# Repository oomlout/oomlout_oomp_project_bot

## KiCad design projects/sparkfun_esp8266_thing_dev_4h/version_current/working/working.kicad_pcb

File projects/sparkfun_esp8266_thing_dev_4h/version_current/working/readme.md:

# ESP8266_Thing_Dev_4H by sparkfun  
This is a harvested standardized copy of a project from github.  
The original project can be found at:  
https://github.com/sparkfun/ESP8266_Thing_Dev_4H  
Please consult that link for additional, details, files, and license information.  
Note: It was auto harvested and if the original repo had more than one board file or anything out of the ordinary the files here are likely not representative.

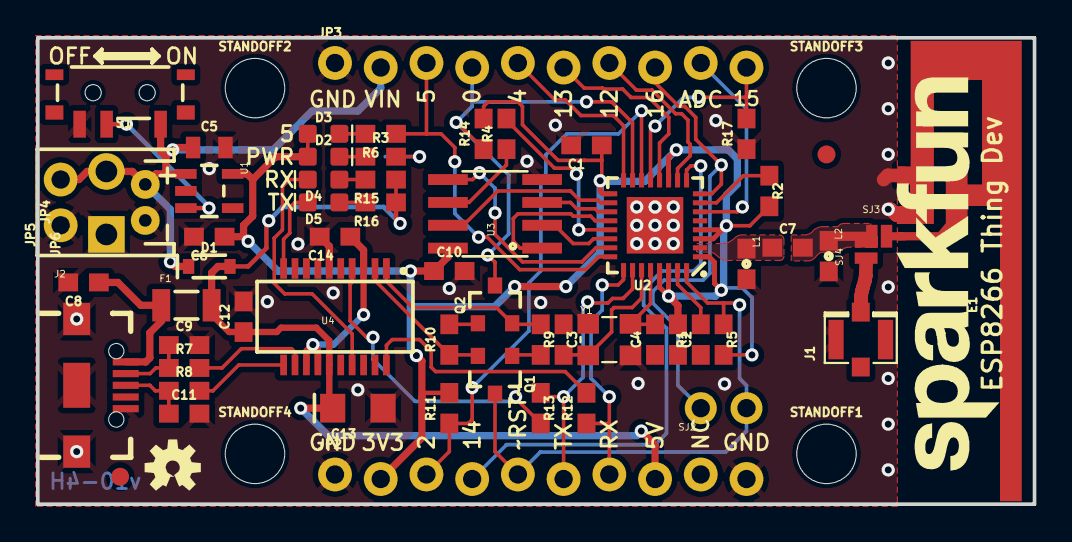
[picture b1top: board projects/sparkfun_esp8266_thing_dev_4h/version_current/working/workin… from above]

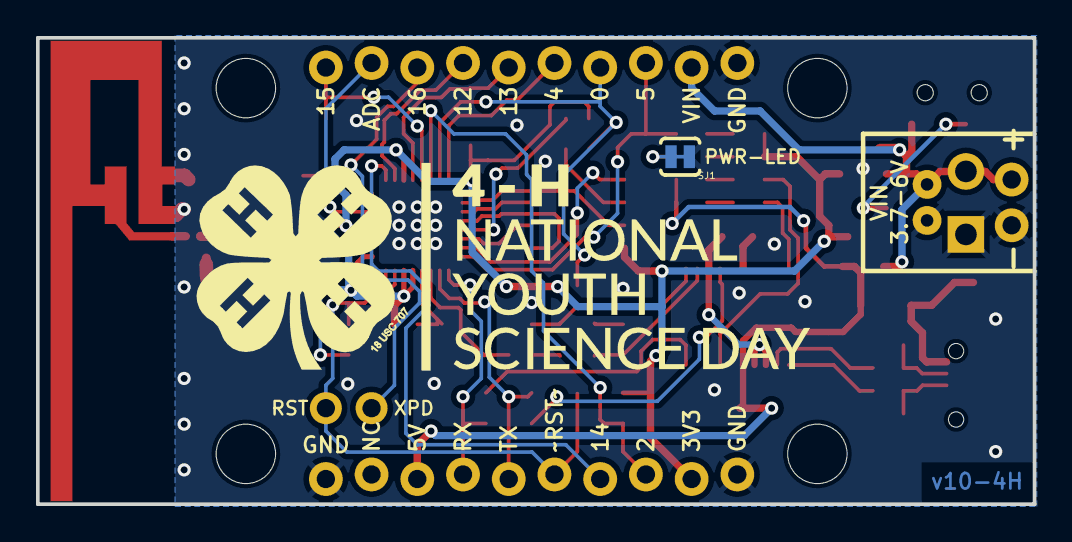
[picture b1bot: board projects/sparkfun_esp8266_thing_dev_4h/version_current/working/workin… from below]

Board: 2 copper layers, 55.4 x 25.9 mm, 70 parts (2 on the bottom side), 52 nets.

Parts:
C1: 10uF; 0603
C2, C8, C10, C12, C14: 0.1uF; 0603
C3, C4: 10pF; 0603
C5: 1.0uF; 0805
C6: 2.2uF; 0603
C7: 5.6PF; 0603
C9, C11: 47pF; 0603
C13: 10uF; EIA3216
D1: 1A/23V/620mV; SOD-323
D2: RED; LED-0603
D3: BLUE; LED-0603
D4: Yellow; LED-0603
D5: GREEN; LED-0603
E1: TRACE_ANTENNA_2.4GHZ_25.7MM
F1: 500mA; PTC-1206
FID1, FID2: FIDUCIAL1X2; FIDUCIAL-1X2
FRAME1: FRAME-LETTER; CREATIVE_COMMONS
J1: U.FL
J2: USB-B-MICRO-SMD_V03
JP2, JP3: 1X10_LOCK_NS
JP4: JST-2-PTH
JP5: 1X02_NO_SILK
JP6: SCREWTERMINAL-3.5MM-2-NS
L1, L2: DNP; 0603
LOGO1: SFE_LOGO_NAME.2_INCH; SFE_LOGO_NAME_.2
LOGO2: OSHW-LOGOS; OSHW-LOGO-S
Q1, Q2: 600mA/40V; SOT23-3
R1: 12k; 0603
R2, R5, R9, R10, R11, R14, R17: 10k; 0603
R3, R4, R6: 200; 0603
R7, R8: 27; 0603
R12, R13, R15, R16: 1k; 0603
S1: SWITCH_SPST_SMD_A
SJ1: PWRLED; PAD-JUMPER-2-NC_BY_TRACE_YES_SILK
SJ2: SLEEP-PTH; PTH-JUMPER-2-NO_NO_SILK
SJ3: TRACE; PAD-JUMPER-2-NC_BY_PASTE_NO_SILK
SJ4: U.FL; PAD-JUMPER-2-NO_NO_SILK
STANDOFF1, STANDOFF2, STANDOFF3, STANDOFF4: STAND-OFF
U1: AP2112K-3.3V; SOT23-5
U2: ESP8266; QFN32-5X5MM
U3: AT25SF041-SOIC8; SO08
U4: FTS31XS-U; SSOP20_L
U$1: 4H-NYSD-LOGO-1.35IN; 4H-1.35IN_WIDE
U$2: SPECIAL_INSTRUCTIONS-ORDERING; ORDERING_INSTRUCTIONS
Y1: 26MHz; CRYSTAL-SMD-3.2X2.5

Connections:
3.3V_F: C14.1, U4.3, U4.13, U4.14
ADC: JP3.9, U2.6
ANT: J1.P$3, SJ4.1
CHIP_EN: R2.1, U2.7
D+: C11.1, J2.D+, R8.1
D-: C9.1, J2.D-, R7.1
DTR: Q2.2, R9.1, U4.1
GND: C1.2, C2.2, C3.1, C4.1, C5.2, C6.2, C8.2, C9.2, C10.2, C11.2, C12.2, C13.-, C14.2, E1.GND, E1.GND2, J1.P$1, J1.P$2, J2.GND, J2.SHIELD1, J2.SHIELD2, J2.SHIELD3, JP2.1, JP2.10, JP3.1, JP4.1, JP5.1, JP6.1, L1.2, L2.2, R1.1, R17.1, S1.1, SJ1.1, U1.2, U2.EP, U3.4, U4.6, U4.16, Y1.2, Y1.4
GPIO0: JP3.4, Q2.3, R14.1, U2.15
GPIO2: JP2.3, R11.1, U2.14
GPIO4: JP3.5, U2.16
GPIO5: JP3.3, R6.1, U2.24
GPIO12: JP3.7, U2.10
GPIO13: JP3.6, U2.12
GPIO14: JP2.4, U2.9
GPIO15: JP3.10, R17.2, U2.13
GPIO16: JP3.8, SJ2.1, U2.8
LNA: C7.1, L1.1, U2.2
LNA2: C7.2, L2.1, SJ3.1, SJ4.2
unnamed: R1.2, U2.31
unnamed: C4.2, U2.28, Y1.3
unnamed: C3.2, U2.27, Y1.1
unnamed: R7.2, U4.12
unnamed: R3.2, SJ1.2
unnamed: Q1.1, R9.2
unnamed: R8.2, U4.11
unnamed: D5.A, R16.2
unnamed: D3.C, R6.2
unnamed: D4.A, R15.2
unnamed: D2.C, R3.1
unnamed: Q2.1, R10.2
unnamed: S1.2, U1.3
RESET: JP2.5, Q1.3, R5.1, SJ2.2, U2.32
RTS: Q1.2, R10.1, U4.2
RXD: R13.2, U4.4
RXLED: D4.C, U4.17
SD_CLK: R4.1, U3.6
SD_CLK0: R4.2, U2.21
SD_CS0: U2.20, U3.1
SD_SI: U2.23, U3.5
SD_SO: U2.22, U3.2
SD_~HD: U2.18, U3.7
SD_~WP: U2.19, U3.3
TRACE_ANT: E1.ANT, SJ3.2
TXD: R12.2, U4.20
TXLED: D5.C, U4.10
U0RXI: JP2.7, R12.1, U2.25
U0TXO: JP2.6, R13.1, U2.26
USBVCC: C12.1, C13.+, D1.A, F1.2, JP2.8, R15.1, R16.1, U4.15
VCC: C1.1, C2.1, C6.1, C10.1, D2.A, D3.A, JP2.2, R2.2, R5.2, R11.2, R14.2, U1.5, U2.1, U2.3, U2.4, U2.11, U2.17, U2.29, U2.30, U3.8
VIN: C5.1, D1.C, JP3.2, JP4.2, JP5.2, JP6.2, S1.3, U1.1
VUSB: C8.1, F1.1, J2.VBUS

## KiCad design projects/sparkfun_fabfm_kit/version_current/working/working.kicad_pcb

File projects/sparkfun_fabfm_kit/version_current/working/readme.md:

# OOMP Project  
## fabFM-Kit  by sparkfun  
  
oomp key: oomp_projects_flat_sparkfun_fabfm_kit  
(snippet of original readme)  
  
**NOTE:** *This product has been retired from our catalog. If you are looking for more up-to-date info, please check out some of these resources to see how other users are still hacking and improving on this product.*  
* *[SparkFun Forum](https://forum.sparkfun.com/)*  
* *[IRC Channel](https://www.sparkfun.com/news/263)*  
  
FabFM Radio Kit  
===============  
  
[    
*FabFM Radio Kit (KIT-11043)*](https://www.sparkfun.com/products/11043)  
  
The FabFM is a stylish FM radio kit that can be built with just basic soldering tools. The PCB is all PTH, meaning that even a beginner solderer can put this kit together with a little time. The wooden, laser cut frame doesn't take any tools or glue to put together, each part press-fits into another. Once assembled the FabFM Radio Kit produces a fully functioning, old-school style FM radio.  
  
[*See the wiki for assembly instuctions.*](https://github.com/sparkfun/fabFM-Kit/wiki)  
  
Repository Contents  
-------------------  
  
* **/enclosure** - Vector files for the enclosure  
* **/firmware** - Arduino sketch that is loaded onto the ATMega328  
* **/hardware** - Eagle PCB layout files  
  
License Information  
-------------------  
  
All contents of this repository are released under [Creative Commons Share-alike 3.0](http://creativecommons.org/licenses/by-sa/3.0/).  
  
Authors: Aaron Weiss @ SparkFun Electonics, Original Design by David Mellis and Dana Gordon  
  
  full source readme at [readme_src.md](readme_src.md)  
  
source repo at: [https://github.com/sparkfun/fabFM-Kit](https://github.com/sparkfun/fabFM-Kit)  
## Board  

## Schematic  

[schematic pdf](working_schematic.pdf)  
## Images

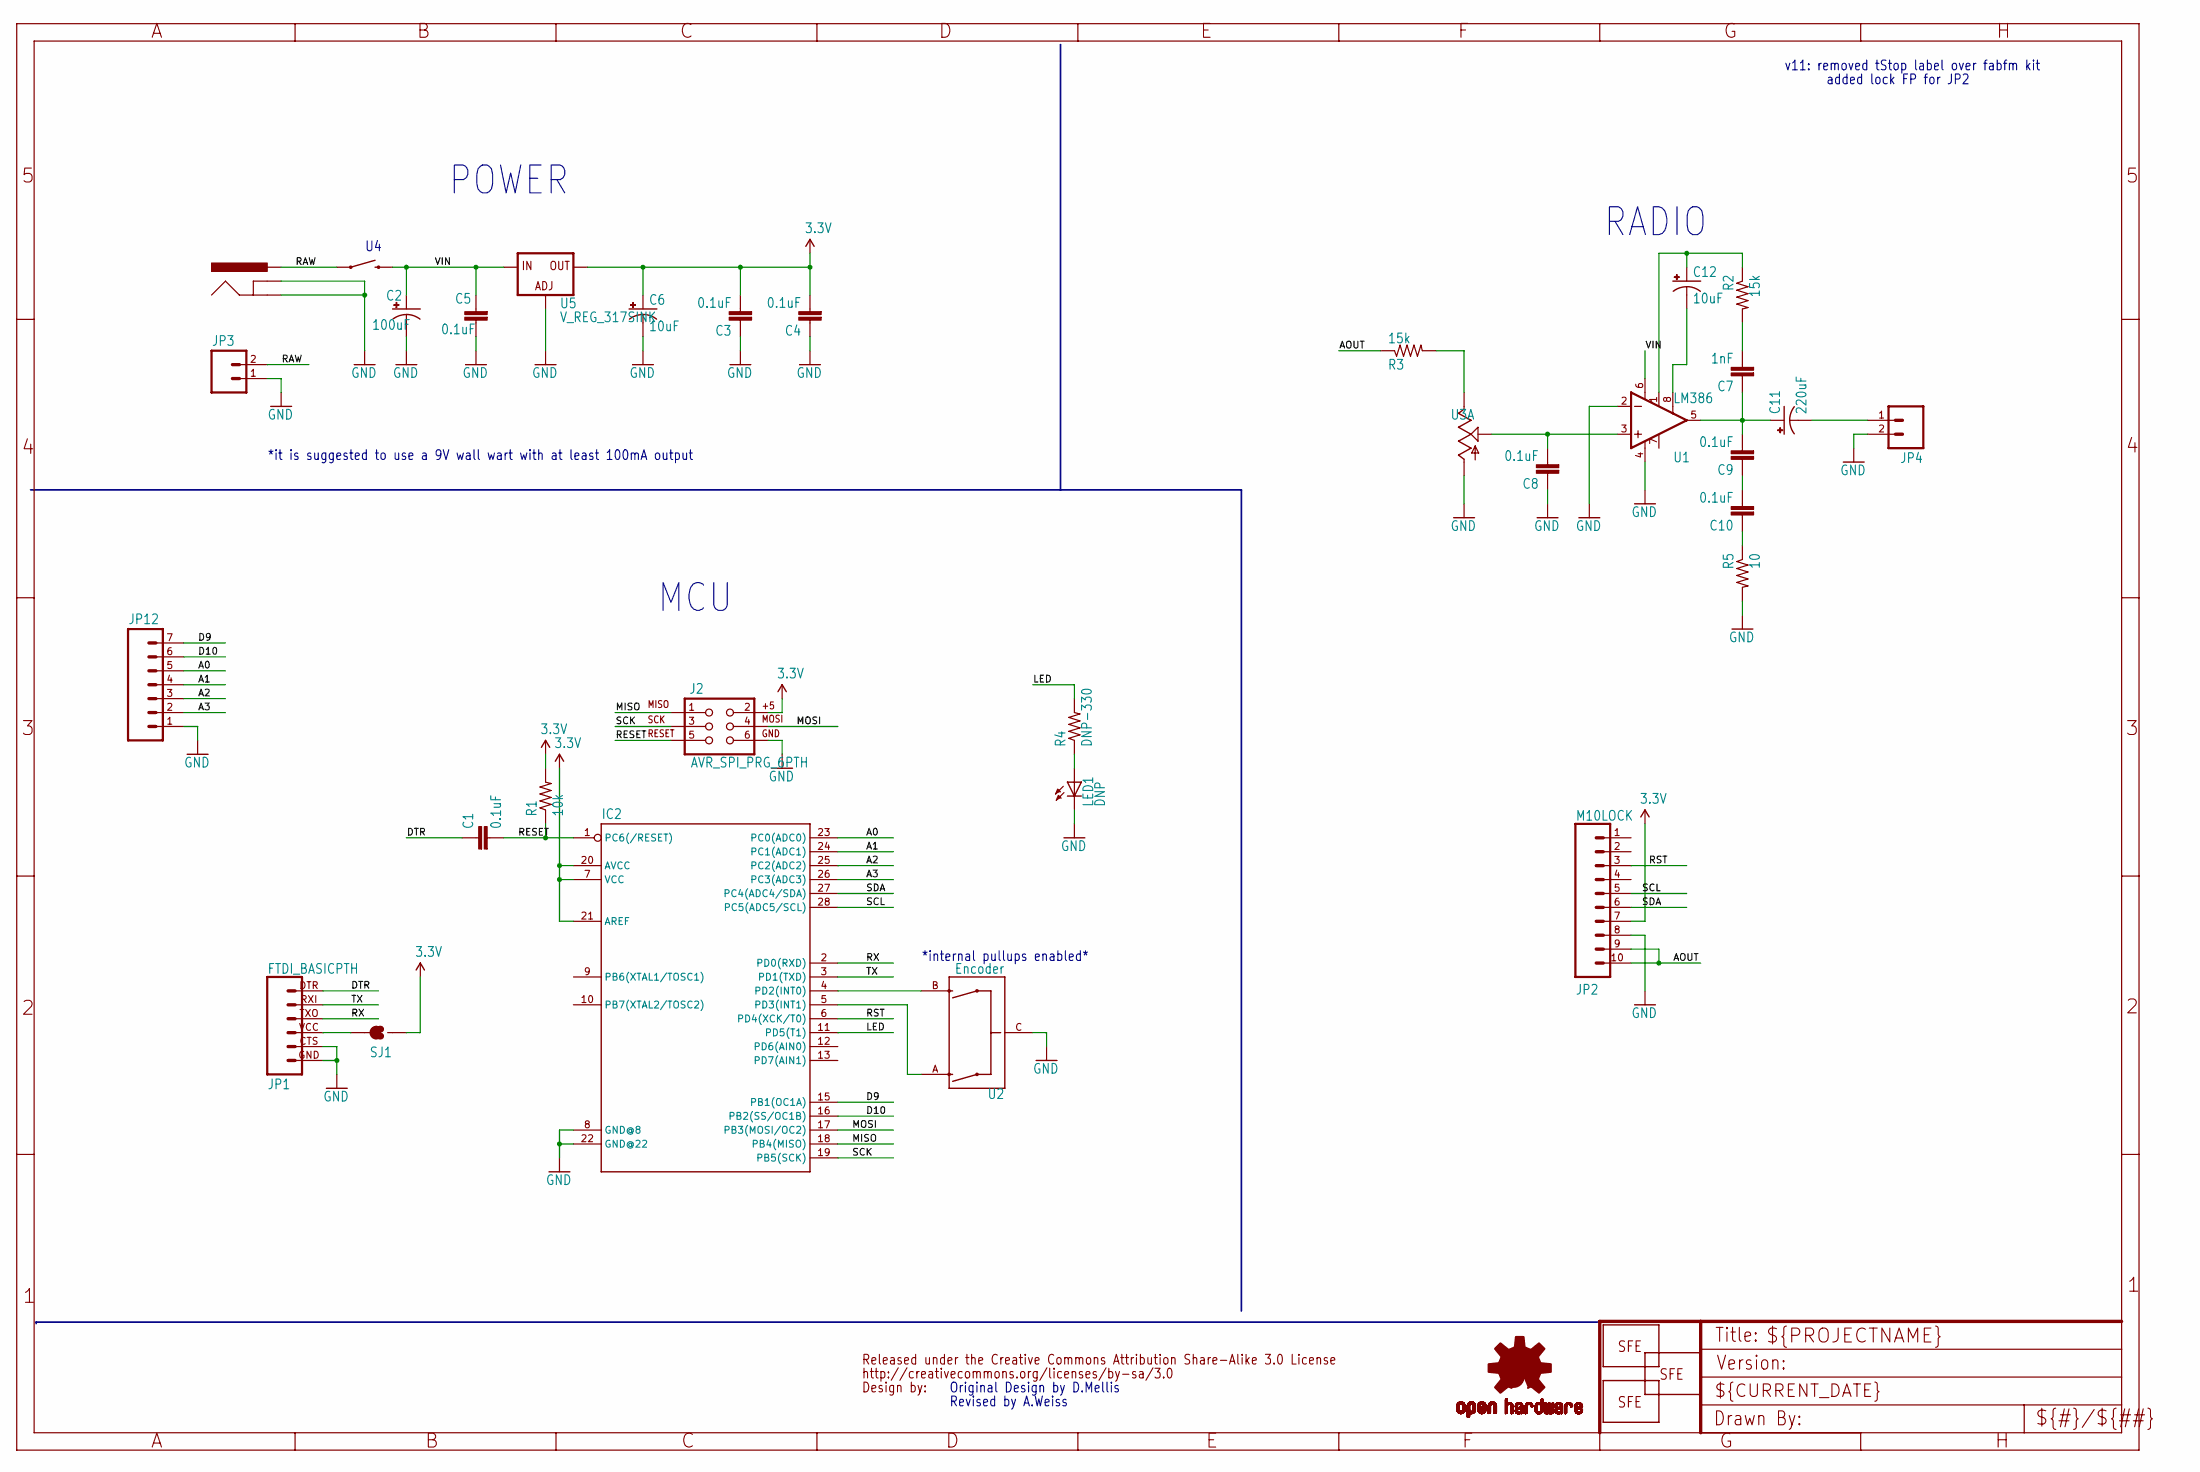
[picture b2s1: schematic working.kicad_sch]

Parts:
C1, C3, C4, C5, C8, C9, C10: 0.1uF; CAP-PTH-SMALL-KIT
C2: 100uF; CPOL-RADIAL-100UF-25V
C6, C12: 10uF; CPOL-RADIAL-10UF-25V
C7: 1nF; CAP-PTH-SMALL-KIT
C11: 220uF; CPOL-RADIAL-100UF-25V
IC2: ATMEGA328P_PDIP_EZ_PB0; DIL28-EZ-PB0
J1: POWER_JACKPTH_LOCK; POWER_JACK_PTH_LOCK
J2: AVR_SPI_PRG_6PTH; 2X3
JP1: FTDI_BASICPTH; FTDI_BASIC
JP2: M10LOCK; 1X10_LOCK
JP3: M02PTH; 1X02
JP4: M02PTH4; 1X02_XTRA_BIG
JP8: LOGO-SFESK; SFE-LOGO-FLAME
JP9, JP11: LOGO-SFENEW; SFE-NEW-WEBLOGO
JP12: M07; 1X07
LED1: DNP; LED3MM
R1: 10k; AXIAL-0.4
R2, R3: 15k; AXIAL-0.4
R4: DNP-330; AXIAL-0.4
R5: 10; AXIAL-0.4
SJ1: SOLDERJUMPERNO; SJ_2S-NO
U1: LM386; DIP08
U2: Encoder; ENCODER-16MM-QUAD
U3: POT_SWITCHPOT_PTH_SWITCH; POT_PTH_SWITCH
U5: V_REG_317SINK; TO220-ADJ
U$1: OSHW-LOGOS; OSHW-LOGO-S
U$2: CREATIVE_COMMONS

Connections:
3.3V: C3.2, C4.2, C6.1 (+), IC2.7 (VCC), IC2.20 (AVCC), IC2.21 (AREF), J2.2, JP2.7, R1.P$2 (2), SJ1.1, U5.OUT
A: IC2.5 (PD3(INT1)), U2.A
A0: IC2.23 (PC0(ADC0)), JP12.5
A1: IC2.24 (PC1(ADC1)), JP12.4
A2: IC2.25 (PC2(ADC2)), JP12.3
A3: IC2.26 (PC3(ADC3)), JP12.2
AOUT: JP2.9, JP2.10, R3.P$1 (1)
B: IC2.4 (PD2(INT0)), U2.B
D9: IC2.15 (PB1(OC1A)), JP12.7
D10: IC2.16 (PB2(SS/OC1B)), JP12.6
DTR: C1.1, JP1.DTR (1)
GND: C2.2 (-), C3.1, C4.1, C5.1, C6.2 (-), C8.1, IC2.8 (GND@8), IC2.22 (GND@22), J1.GND, J1.GNDBREAK, J2.6, JP1.CTS (5), JP1.GND (6), JP2.8, JP3.1, JP4.2, JP12.1, LED1.K (C), R5.P$2 (2), U1.2 (-IN), U1.4 (V-), U2.C, U3.1 (A), U5.ADJ
LED: IC2.11 (PD5(T1)), R4.P$2 (2)
MISO: IC2.18 (PB4(MISO)), J2.1
MOSI: IC2.17 (PB3(MOSI/OC2)), J2.4
unnamed: LED1.A, R4.P$1 (1)
unnamed: C8.2, U1.3 (+IN), U3.2 (S)
unnamed: C7.1, C9.2, C11.1 (+), U1.5 (OUT)
unnamed: C12.1 (+), R2.P$1 (1), U1.1 (GAIN@1)
unnamed: C11.2 (-), JP4.1
unnamed: C9.1, C10.2
unnamed: C10.1, R5.P$1 (1)
unnamed: C12.2 (-), U1.8 (GAIN@8)
unnamed: C7.2, R2.P$2 (2)
unnamed: R3.P$2 (2), U3.3 (E)
unnamed: JP1.VCC (4), SJ1.2
RAW: J1.PWR, JP3.2, U3.S1 (1)
RESET: C1.2, IC2.1 (PC6(/RESET)), J2.5, R1.P$1 (1)
RST: IC2.6 (PD4(XCK/T0)), JP2.3
RX: IC2.2 (PD0(RXD)), JP1.TXO (3)
SCK: IC2.19 (PB5(SCK)), J2.3
SCL: IC2.28 (PC5(ADC5/SCL)), JP2.5
SDA: IC2.27 (PC4(ADC4/SDA)), JP2.6
TX: IC2.3 (PD1(TXD)), JP1.RXI (2)
VIN: C2.1 (+), C5.2, U1.6 (V+), U3.S2 (2), U5.IN

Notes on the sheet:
*internal pullups enabled*
*it is suggested to use a 9V wall wart with at least 100mA output
Revised by A.Weiss
MCU
added lock FP for JP2
POWER
RADIO
v11: removed tStop label over fabfm kit
Original Design by D.Mellis

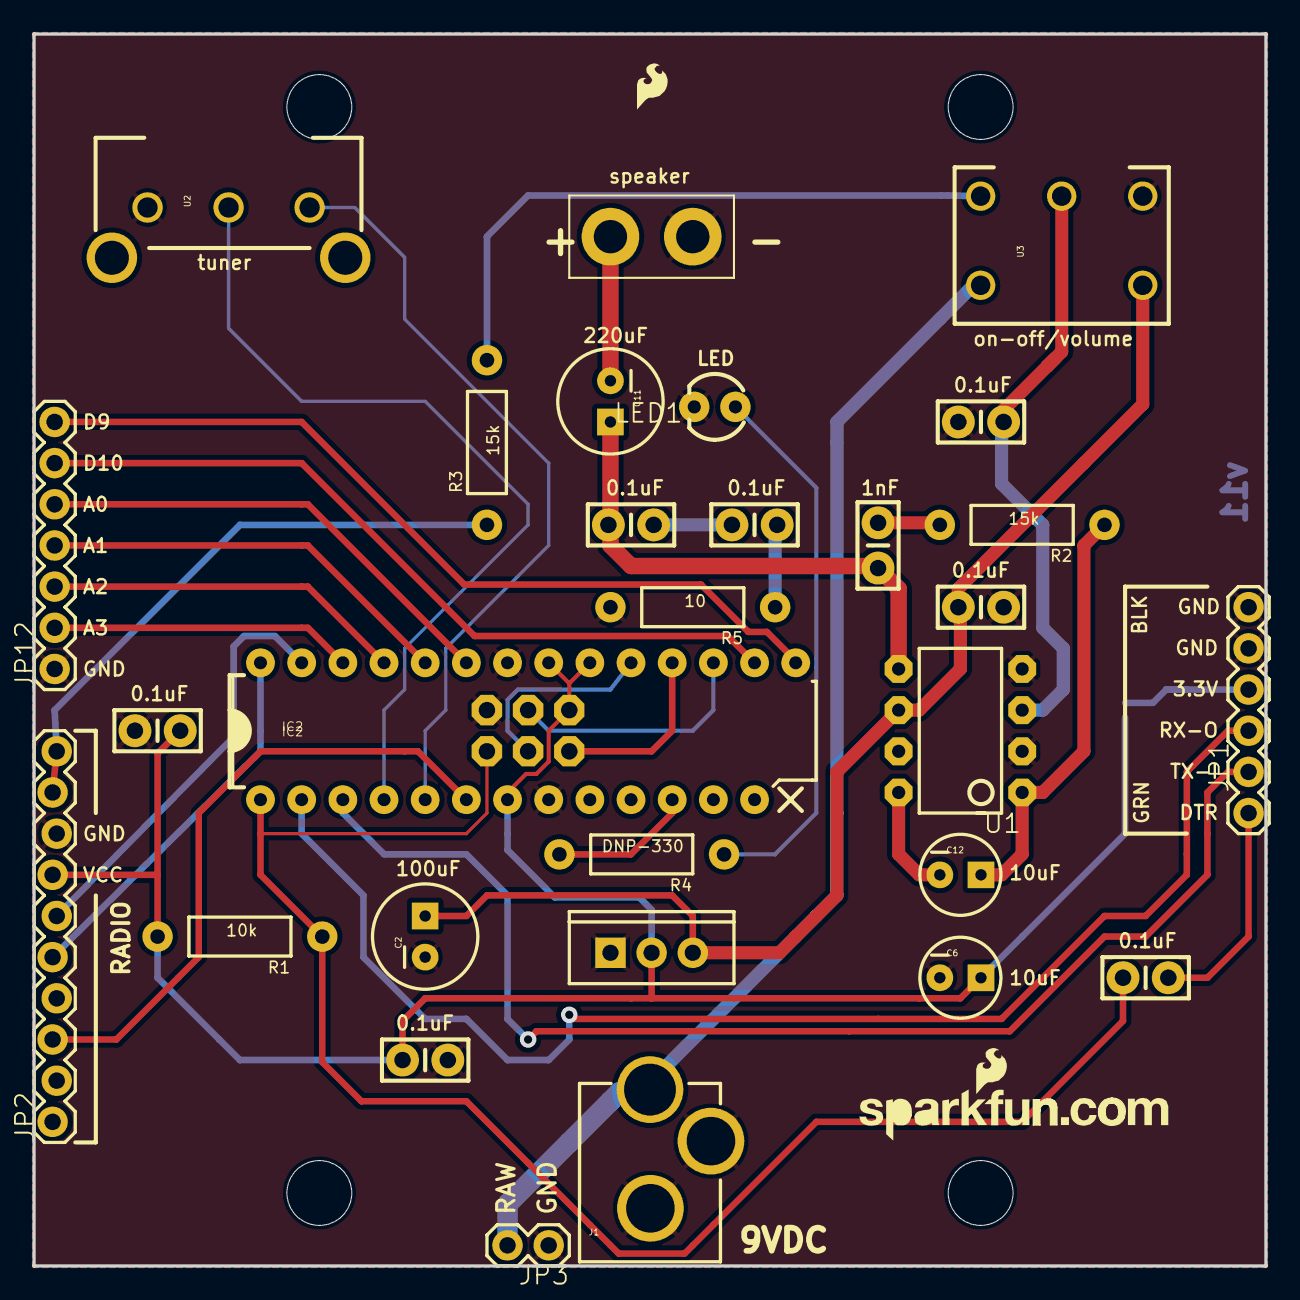
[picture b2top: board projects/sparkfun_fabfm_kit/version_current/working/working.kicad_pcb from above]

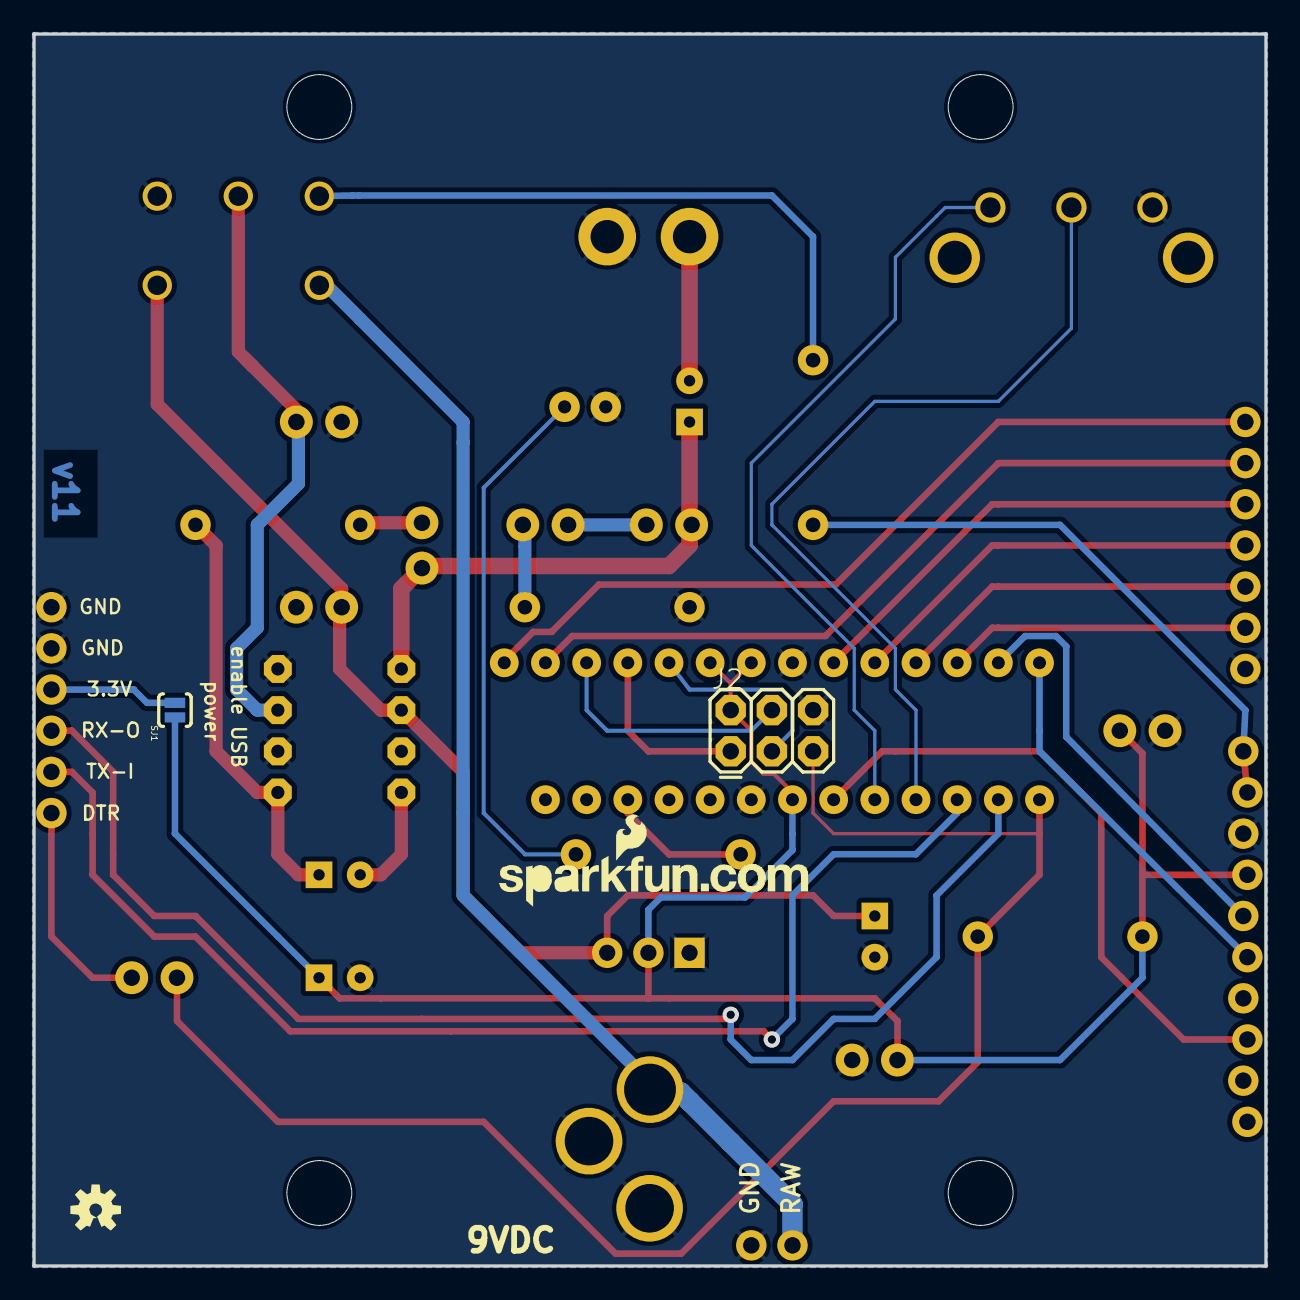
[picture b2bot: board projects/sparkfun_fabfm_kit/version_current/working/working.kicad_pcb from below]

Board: 2 copper layers, 76.0 x 76.0 mm, 40 parts (4 on the bottom side), 35 nets.

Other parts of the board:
@HOLE0, @HOLE1, @HOLE2, @HOLE3: (no value)

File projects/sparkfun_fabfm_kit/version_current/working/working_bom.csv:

Row,Description,Part,References,Value,Footprint,Quantity Per PCB,Status,Datasheet
1,,CAPKIT,C7,1nF,CAP-PTH-SMALL-KIT,1, ,
2,,CAPKIT,C1 C3 C4 C5 C8 C9 C10,0.1uF,CAP-PTH-SMALL-KIT,7, ,
3,,CAP_POLPTH2,C6 C12,10uF,CPOL-RADIAL-10UF-25V,2, ,
4,,CAP_POLPTH1,C2,100uF,CPOL-RADIAL-100UF-25V,1, ,
5,,CAP_POLPTH1,C11,220uF,CPOL-RADIAL-100UF-25V,1, ,
6,,ATMEGA328P_PDIP_EZ_PB0,IC2,ATMEGA328P_PDIP_EZ_PB0,DIL28-EZ-PB0,1, ,
7,,AVR_SPI_PRG_6PTH,J2,AVR_SPI_PRG_6PTH,2X3,1, ,
8,,POWER_JACKPTH_LOCK,J1,POWER_JACKPTH_LOCK,POWER_JACK_PTH_LOCK,1, ,
9,,FTDI_BASICPTH,JP1,FTDI_BASICPTH,FTDI_BASIC,1, ,
10,,LOGO-SFENEW,JP9 JP11,LOGO-SFENEW,SFE-NEW-WEBLOGO,2, ,
11,,LOGO-SFESK,JP8,LOGO-SFESK,SFE-LOGO-FLAME,1, ,
12,,M02PTH,JP3,M02PTH,1X02,1, ,
13,,M02PTH4,JP4,M02PTH4,1X02_XTRA_BIG,1, ,
14,,M07,JP12,M07,1X07,1, ,
15,,M10LOCK,JP2,M10LOCK,1X10_LOCK,1, ,
16,,RESISTORPTH-1/4W,R5,10,AXIAL-0.4,1, ,
17,,RESISTORPTH-1/4W,R1,10k,AXIAL-0.4,1, ,
18,,RESISTORPTH-1/4W,R2 R3,15k,AXIAL-0.4,2, ,
19,,RESISTORPTH-1/4W,R4,DNP-330,AXIAL-0.4,1, ,
20,,ENCODER-QUADRATURE,U2,Encoder,ENCODER-16MM-QUAD,1, ,
21,,LM386,U1,LM386,DIP08,1, ,
22,,POT_SWITCHPOT_PTH_SWITCH,U3,POT_SWITCHPOT_PTH_SWITCH,POT_PTH_SWITCH,1, ,
23,,V_REG_317SINK,U5,V_REG_317SINK,TO220-ADJ,1, ,
24,,CREATIVE_COMMONS,U$2,CREATIVE_COMMONS,CREATIVE_COMMONS,1, ,
25,,OSHW-LOGOS,U$1,OSHW-LOGOS,OSHW-LOGO-S,1, ,





Project info:
Schematic:,working
Variant:,default
Revision:,
Date:,2023-08-06_12-56-02
KiCad Version:,7.0.6-7.0.6~ubuntu22.04.1
Statistics:
Component Groups:,26
Component Count:,35 (0 SMD/ 0 THT)
Fitted Components:,34 (0 SMD/ 0 THT)
Number of PCBs:,1
Total Components:,34

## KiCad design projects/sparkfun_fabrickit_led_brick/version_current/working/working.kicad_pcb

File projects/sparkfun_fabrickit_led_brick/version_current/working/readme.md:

# Fabrickit_LED_Brick by sparkfun  
This is a harvested standardized copy of a project from github.  
The original project can be found at:  
https://github.com/sparkfun/Fabrickit_LED_Brick  
Please consult that link for additional, details, files, and license information.  
Note: It was auto harvested and if the original repo had more than one board file or anything out of the ordinary the files here are likely not representative.

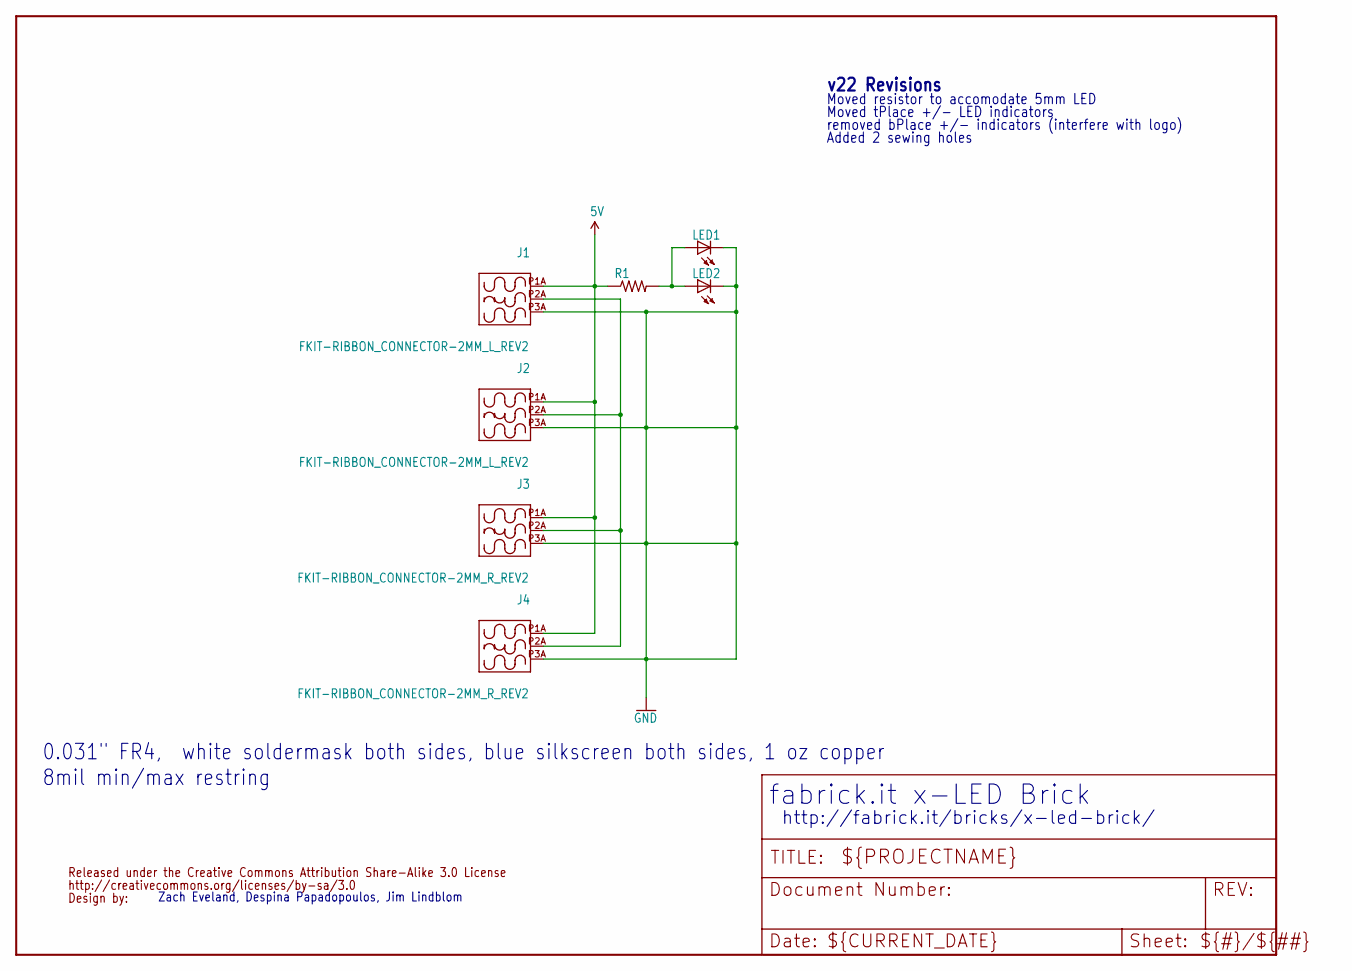
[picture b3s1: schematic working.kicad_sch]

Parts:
J1, J2: FKIT-RIBBON_CONNECTOR-2MM_L_REV2; FKIT-RIBBON_CONNECTOR_03_2MM_L
J3, J4: FKIT-RIBBON_CONNECTOR-2MM_R_REV2; FKIT-RIBBON_CONNECTOR_03_2MM_R
LED1: LED; FKIT-LED-1206_NO_CREAM
LED2: LED-3MM-NO_SILK; LED3MM-NS
R1: RESISTOR0603; 0603-RES
U$1: CREATIVE_COMMONS

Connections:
5V: J1.P1A, J2.P1A, J3.P1A, J4.P1A, R1.1
GND: J1.P3A, J2.P3A, J3.P3A, J4.P3A, LED1.C, LED2.K (C)
unnamed: J1.P2A, J2.P2A, J3.P2A, J4.P2A
unnamed: LED1.A, LED2.A, R1.2

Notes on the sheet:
v22 Revisions
http://fabrick.it/bricks/x-led-brick/
Moved tPlace +/- LED indicators
Added 2 sewing holes
removed bPlace +/- indicators (interfere with logo)
Zach Eveland, Despina Papadopoulos, Jim Lindblom
fabrick.it x-LED Brick
0.031" FR4, white soldermask both sides, blue silkscreen both sides, 1 oz copper
8mil min/max restring
Moved resistor to accomodate 5mm LED

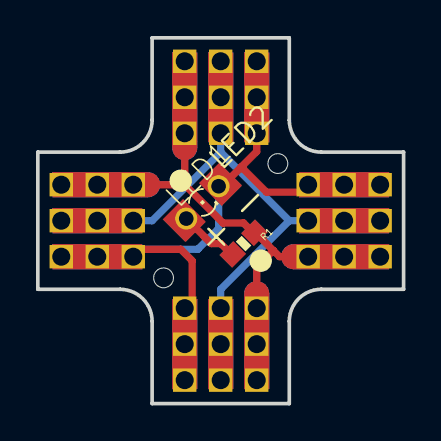
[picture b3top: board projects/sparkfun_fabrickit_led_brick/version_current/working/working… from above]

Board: 2 copper layers, 20.3 x 20.3 mm, 10 parts (0 on the bottom side), 4 nets.

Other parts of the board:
@HOLE0, @HOLE1: (no value)

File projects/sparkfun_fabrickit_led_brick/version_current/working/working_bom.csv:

Row,Description,Part,References,Value,Footprint,Quantity Per PCB,Status,Datasheet
1,,FKIT-RIBBON_CONNECTOR-2MM_L_REV2,J1 J2,FKIT-RIBBON_CONNECTOR-2MM_L_REV2,FKIT-RIBBON_CONNECTOR_03_2MM_L,2, ,
2,,FKIT-RIBBON_CONNECTOR-2MM_R_REV2,J3 J4,FKIT-RIBBON_CONNECTOR-2MM_R_REV2,FKIT-RIBBON_CONNECTOR_03_2MM_R,2, ,
3,,LED,LED1,LED,FKIT-LED-1206_NO_CREAM,1, ,
4,,LED-3MM-NO_SILK,LED2,LED-3MM-NO_SILK,LED3MM-NS,1, ,
5,,RESISTOR0603,R1,RESISTOR0603,0603-RES,1, ,
6,,CREATIVE_COMMONS,U$1,CREATIVE_COMMONS,CREATIVE_COMMONS,1, ,





Project info:
Schematic:,working
Variant:,default
Revision:,
Date:,2023-08-06_12-56-02
KiCad Version:,7.0.6-7.0.6~ubuntu22.04.1
Statistics:
Component Groups:,6
Component Count:,8 (0 SMD/ 0 THT)
Fitted Components:,8 (0 SMD/ 0 THT)
Number of PCBs:,1
Total Components:,8

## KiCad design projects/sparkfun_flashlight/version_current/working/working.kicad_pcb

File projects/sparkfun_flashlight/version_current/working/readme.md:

# Flashlight by sparkfun  
This is a harvested standardized copy of a project from github.  
The original project can be found at:  
https://github.com/sparkfun/Flashlight  
Please consult that link for additional, details, files, and license information.  
Note: It was auto harvested and if the original repo had more than one board file or anything out of the ordinary the files here are likely not representative.

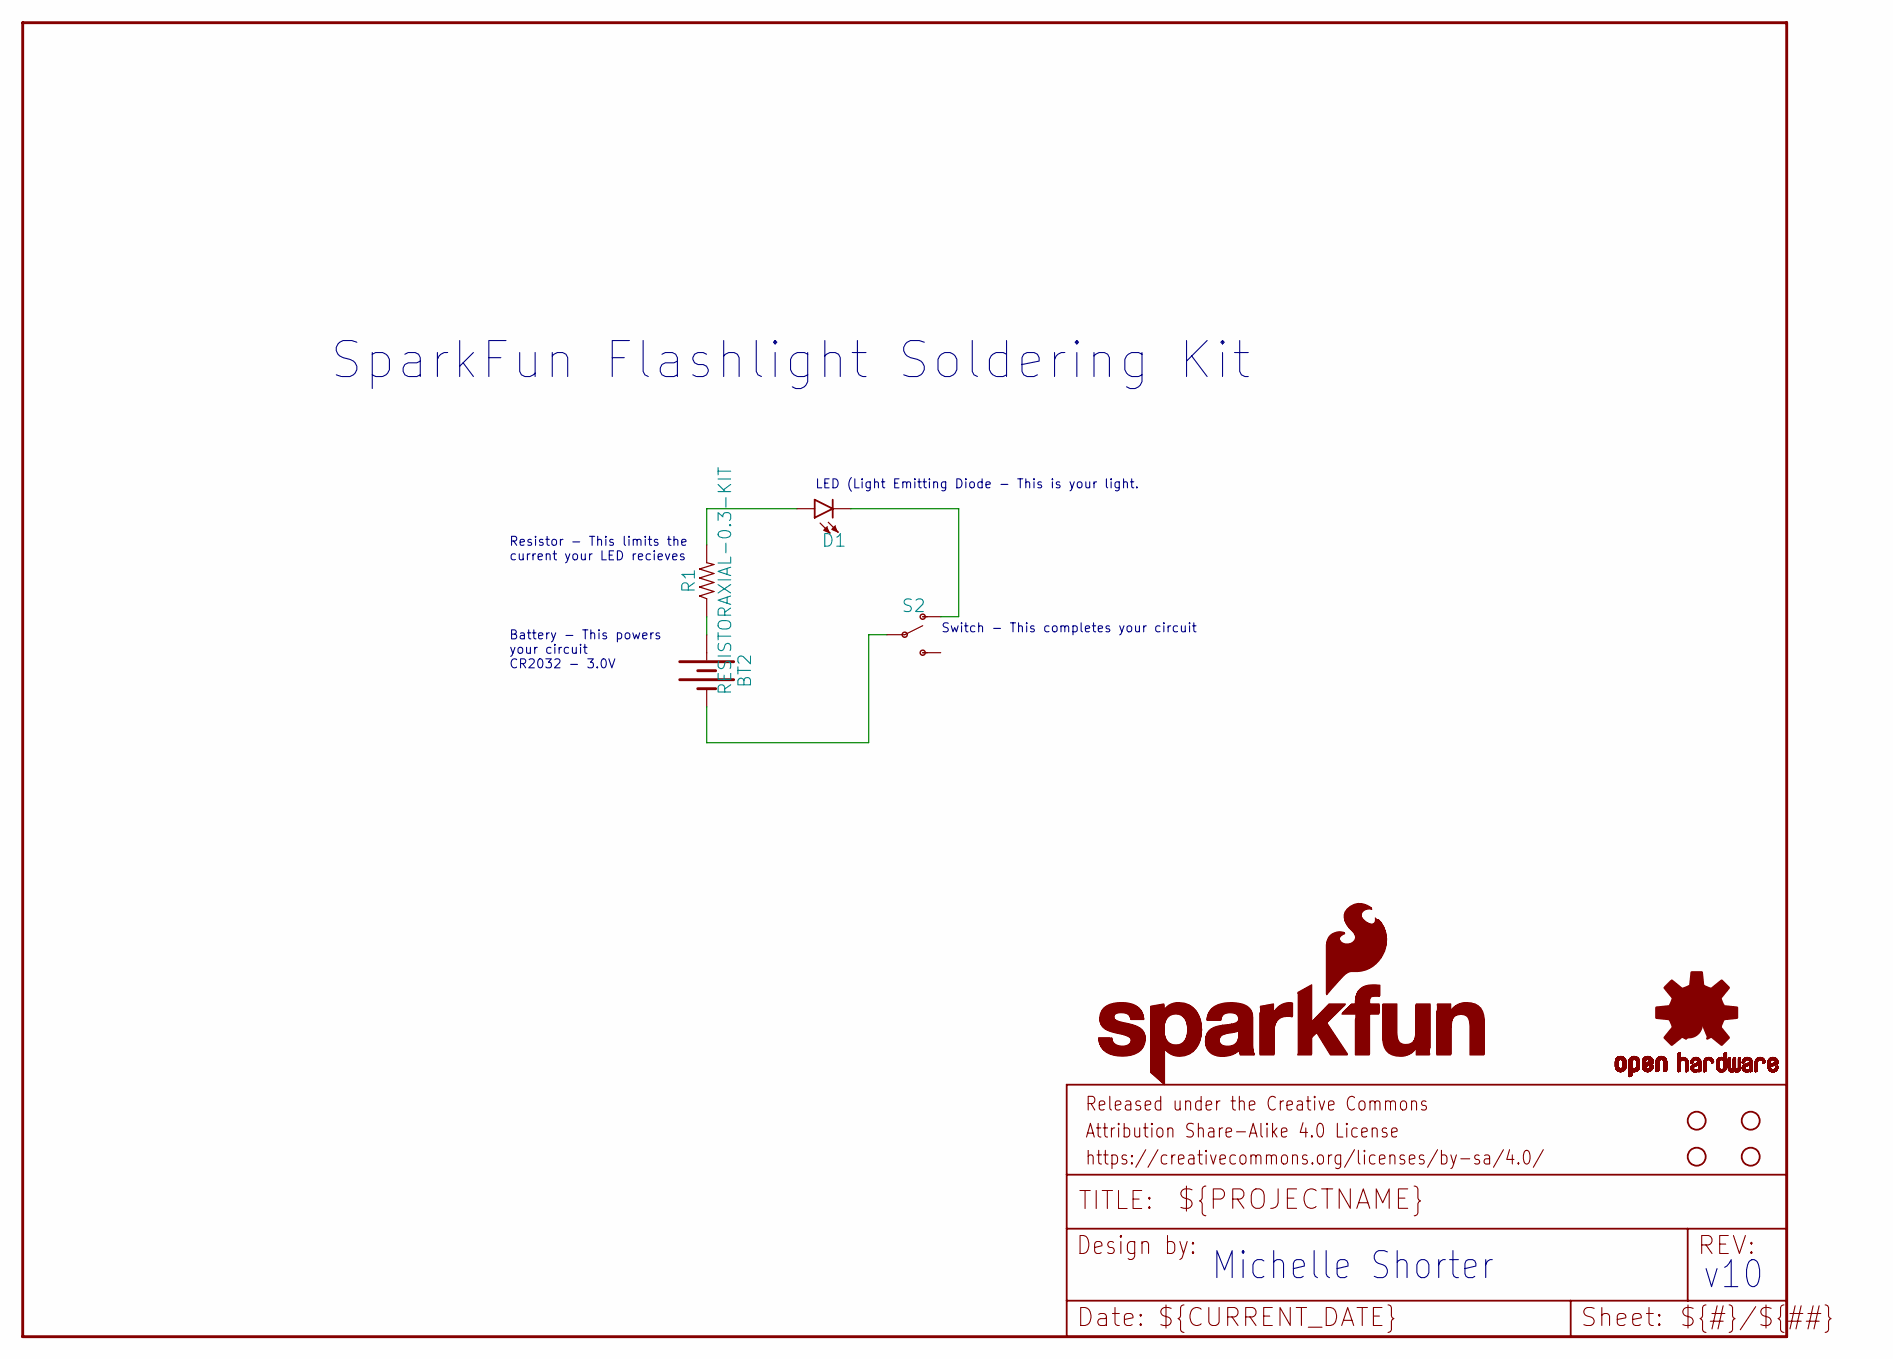
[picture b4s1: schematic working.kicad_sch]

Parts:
BT2: BATTERY-20MM_PTH_KIT; BATTCOM_20MM_PTH_KIT
D1: LED-5MM-KIT-NO-SILK; LED_5MM-KIT-NO-SILK
FRAME1: FRAME-LETTER; CREATIVE_COMMONS
H1, H2, H3, H4: STAND-OFF
LOGO1: OSHW-LOGOS; OSHW-LOGO-S
LOGO2: SFE_LOGO_FLAME.1_INCH; SFE_LOGO_FLAME_.1
LOGO3: SFE_LOGO_NAME_FLAME.2_INCH; SFE_LOGO_NAME_FLAME_.2
LOGO4: SFE_LOGO_NAME.2_INCH; SFE_LOGO_NAME_.2
R1: RESISTORAXIAL-0.3-KIT; AXIAL-0.3-KIT
S2: SWITCH-SPDT-PTH-11.6X4.0MM-KIT; SWITCH_SPDT_PTH_11.6X4.0MM_KIT

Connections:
ANODE: D1.K (C), S2.1 (O)
CATHODE: BT2.1 (+), R1.P$1 (1)
GND: D1.A, R1.P$2 (2)
unnamed: BT2.2 (-), S2.2

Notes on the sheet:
v10
Resistor - This limits the current your LED recieves
Switch - This completes your circuit
SparkFun Flashlight Soldering Kit
LED (Light Emitting Diode - This is your light.
Michelle Shorter
Battery - This powers your circuit CR2032 - 3.0V

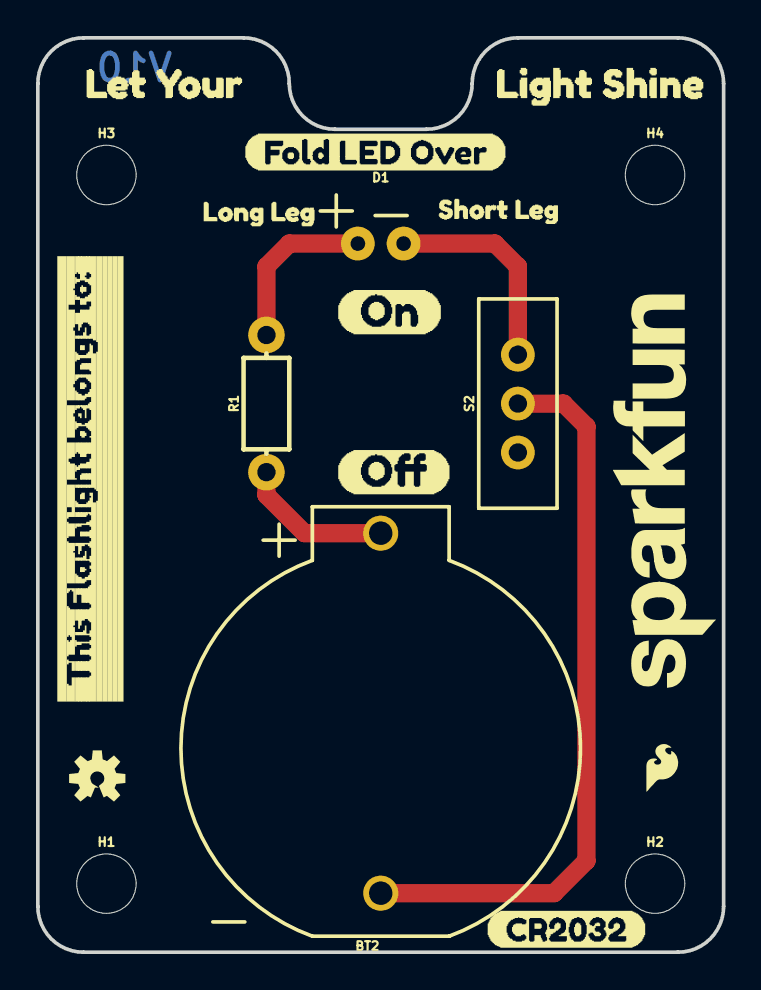
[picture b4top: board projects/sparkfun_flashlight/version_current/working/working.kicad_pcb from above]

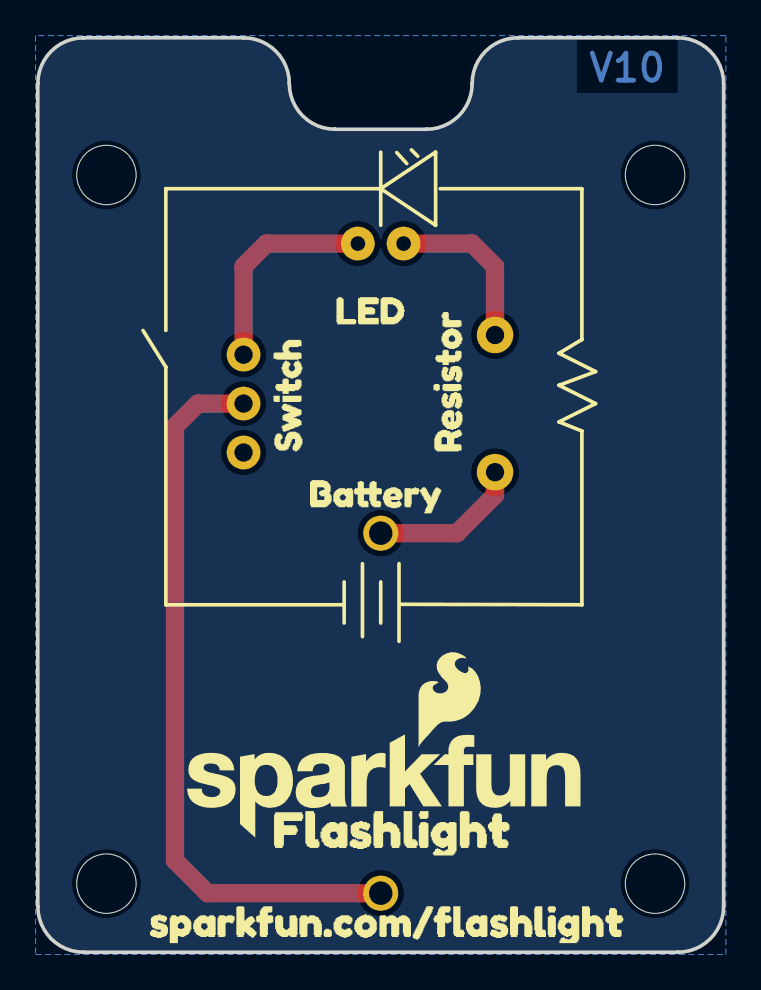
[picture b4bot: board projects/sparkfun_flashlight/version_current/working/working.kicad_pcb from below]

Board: 2 copper layers, 38.1 x 50.8 mm, 28 parts (7 on the bottom side), 4 nets.

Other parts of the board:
U$1: CR20325
U$2: FLASHLIGHT6
U$3: FOLD_LED_OVER0
U$4: BATTERY11
U$5: LET_YOUR11
U$6: LIGHT_SHINE12
U$7: LONG_LEG2
U$8: OFF4
U$9: ON3
U$10: SHORT_LEG1
U$11: SPARKFUN#COM#FLASHLIGHT13
U$12: LED12
U$13: THIS_FLASHLIGHT_BELONGS_TO#10
U$14: RESISTOR14
U$15: SWITCH13

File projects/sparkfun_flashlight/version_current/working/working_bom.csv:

"Id";"Designator";"Footprint";"Quantity";"Designation";"Supplier and ref";
1;"U$7";"LONG_LEG2";1;"";;;
2;"FRAME1";"CREATIVE_COMMONS";1;"FRAME-LETTER";;;
3;"H3,H2,H1,H4";"STAND-OFF";4;"STAND-OFF";;;
4;"LOGO1";"OSHW-LOGO-S";1;"OSHW-LOGOS";;;
5;"U$1";"CR20325";1;"";;;
6;"R1";"AXIAL-0.3-KIT";1;"10";;;
7;"U$13";"THIS_FLASHLIGHT_BELONGS_TO#10";1;"";;;
8;"LOGO4";"SFE_LOGO_NAME_.2";1;"SFE_LOGO_NAME.2_INCH";;;
9;"U$3";"FOLD_LED_OVER0";1;"";;;
10;"U$6";"LIGHT_SHINE12";1;"";;;
11;"U$8";"OFF4";1;"";;;
12;"D1";"LED_5MM-KIT-NO-SILK";1;"";;;
13;"U$9";"ON3";1;"";;;
14;"U$10";"SHORT_LEG1";1;"";;;
15;"BT2";"BATTCOM_20MM_PTH_KIT";1;"";;;
16;"U$5";"LET_YOUR11";1;"";;;
17;"S2";"SWITCH_SPDT_PTH_11.6X4.0MM_KIT";1;"";;;
18;"LOGO2";"SFE_LOGO_FLAME_.1";1;"SFE_LOGO_FLAME.1_INCH";;;
19;"U$14";"RESISTOR14";1;"";;;
20;"U$12";"LED12";1;"";;;
21;"LOGO3";"SFE_LOGO_NAME_FLAME_.2";1;"SFE_LOGO_NAME_FLAME.2_INCH";;;
22;"U$2";"FLASHLIGHT6";1;"";;;
23;"U$15";"SWITCH13";1;"";;;
24;"U$11";"SPARKFUN#COM#FLASHLIGHT13";1;"";;;
25;"U$4";"BATTERY11";1;"";;;

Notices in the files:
projects/sparkfun_esp8266_thing_dev_4h/version_current/working/working.kicad_sch:
Released under the Creative Commons
projects/sparkfun_fabfm_kit/version_current/working/working.kicad_sch:
Released under the Creative Commons Attribution Share-Alike 3.0 License
parts and their libraries:
Released under the Creative Commons Attribution Share-Alike 4.0 License
